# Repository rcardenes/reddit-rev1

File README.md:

Reddit review
=============

Some guy at Reddit asked for some help routing some schematic he came up with. I'm by no
means an expert, but here's my try at it.

It's bit packed (resistors too close to each other, I guess), but I went for compactness
and I don't expect the signals to be high speed by any definition. The point here was
just to show a way to route that big bunch of traces between the 74LS574s.

Top:

Bottom:

Model:

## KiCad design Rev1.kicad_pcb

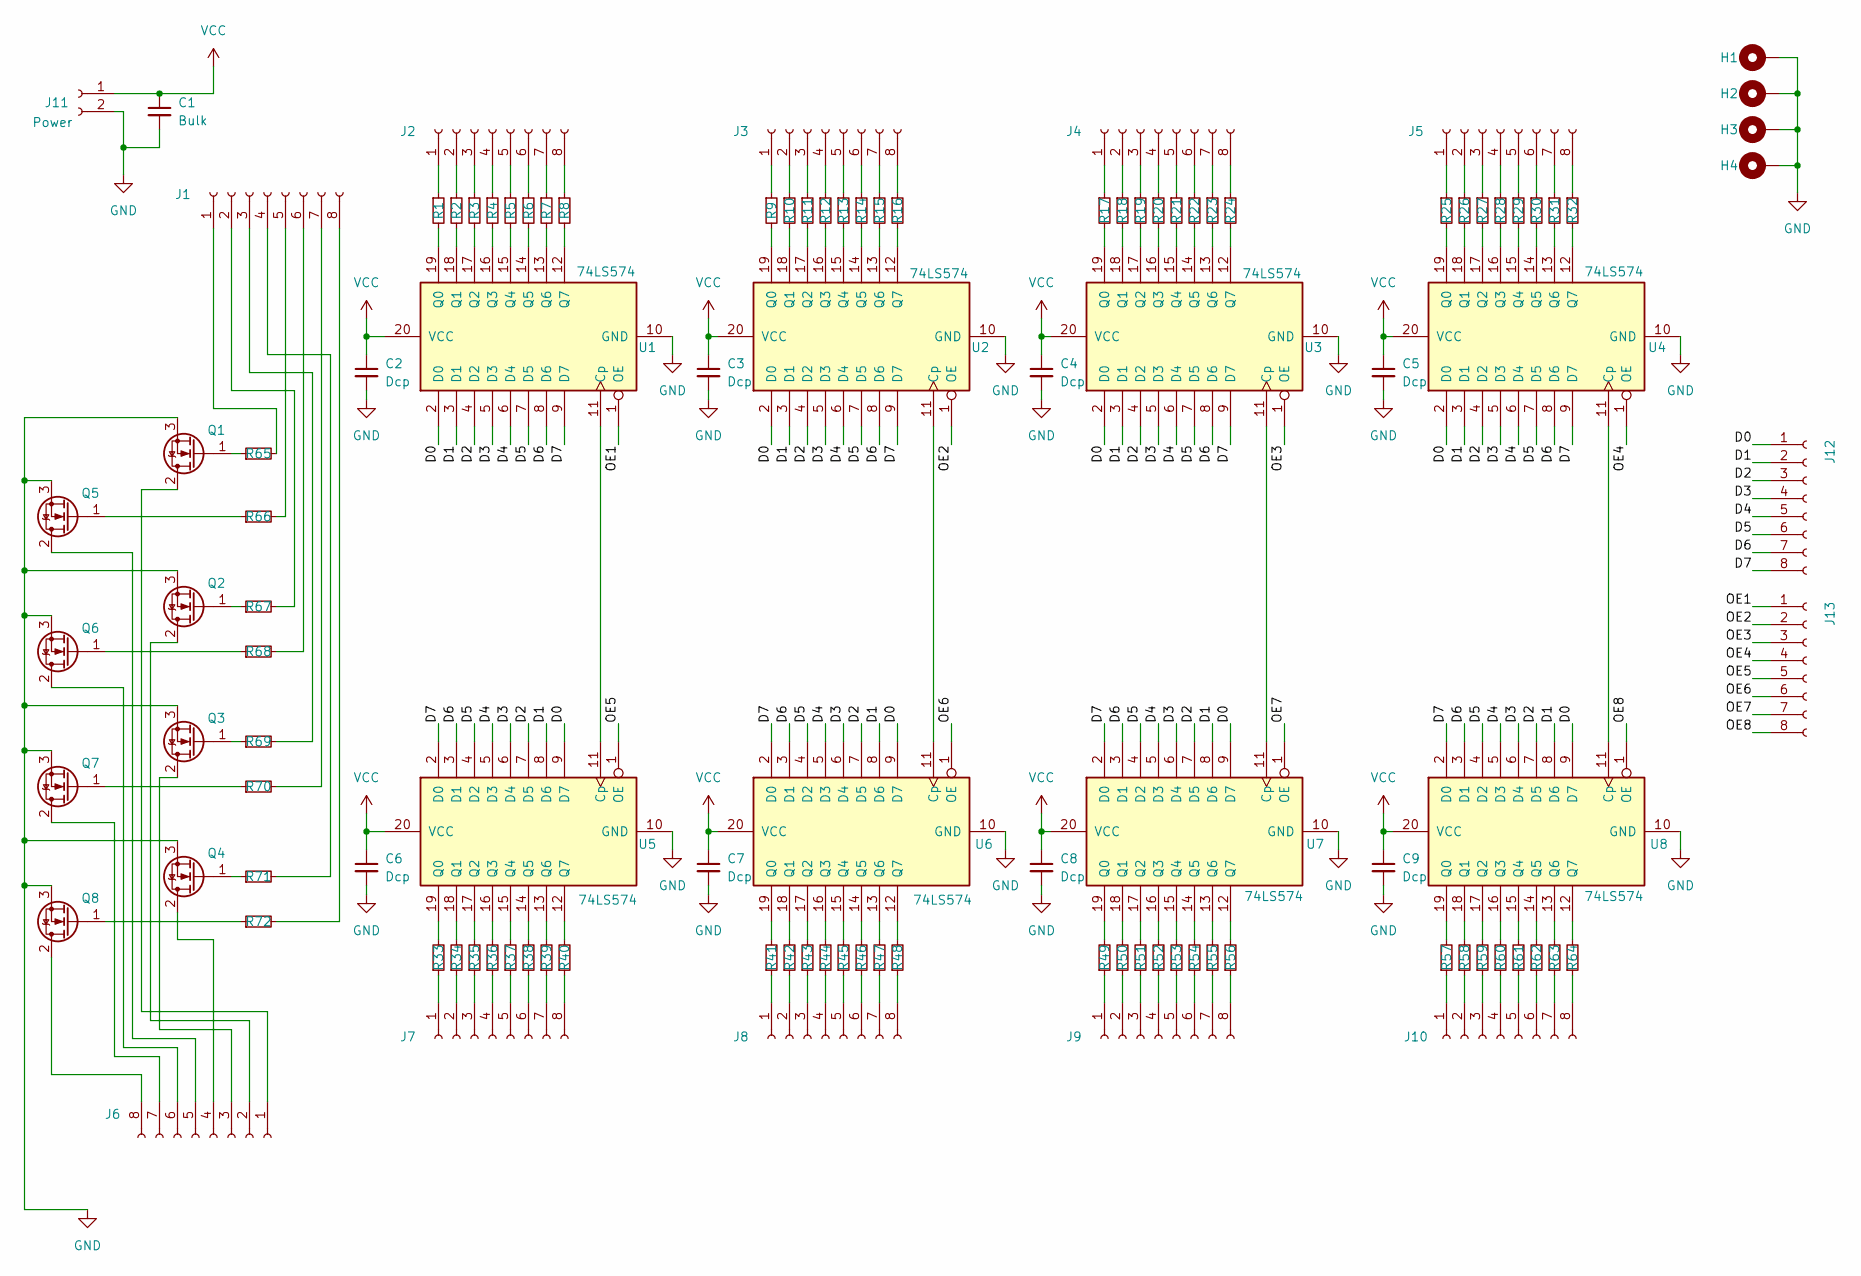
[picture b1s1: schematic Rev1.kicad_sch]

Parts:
C1: Bulk; C_Radial_D6.3mm_H7.0mm_P2.50mm
C2, C3, C4, C5, C6, C7, C8, C9: Dcp; C_Disc_D3.0mm_W2.0mm_P2.50mm
H1, H2, H3, H4: MountingHole_Pad; MountingHole_2.2mm_M2_Pad
J1, J2, J3, J4, J5, J6, J7, J8, J9, J10, J12, J13: Conn_01x08_Socket; PinHeader_1x08_P1.27mm_Vertical
J11: Power; PinHeader_1x02_P1.27mm_Vertical
Q1, Q2, Q3, Q4, Q5, Q6, Q7, Q8: IRF540N; TO-220-3_Vertical
R1, R2, R3, R4, R5, R6, R7, R8, R9, R10, R11, R12, R13, R14, R15, R16, R17, R18, R19, R20, R21, R22, R23, R24, R25, R26, R27, R28, R29, R30, R31, R32, R33, R34, R35, R36, R37, R38, R39, R40, R41, R42, R43, R44, R45, R46, R47, R48, R49, R50, R51, R52, R53, R54, R55, R56, R57, R58, R59, R60, R61, R62, R63, R64, R65, R66, R67, R68, R69, R70, R71, R72: R_Small; R_Axial_DIN0204_L3.6mm_D1.6mm_P5.08mm_Horizontal
U1, U2, U3, U4, U5, U6, U7, U8: 74LS574; DIP-20_W7.62mm

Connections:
/D0: J12.1, U1.2 (D0), U2.2 (D0), U3.2 (D0), U4.2 (D0), U5.9 (D7), U6.9 (D7), U7.9 (D7), U8.9 (D7)
/D1: J12.2, U1.3 (D1), U2.3 (D1), U3.3 (D1), U4.3 (D1), U5.8 (D6), U6.8 (D6), U7.8 (D6), U8.8 (D6)
/D2: J12.3, U1.4 (D2), U2.4 (D2), U3.4 (D2), U4.4 (D2), U5.7 (D5), U6.7 (D5), U7.7 (D5), U8.7 (D5)
/D3: J12.4, U1.5 (D3), U2.5 (D3), U3.5 (D3), U4.5 (D3), U5.6 (D4), U6.6 (D4), U7.6 (D4), U8.6 (D4)
/D4: J12.5, U1.6 (D4), U2.6 (D4), U3.6 (D4), U4.6 (D4), U5.5 (D3), U6.5 (D3), U7.5 (D3), U8.5 (D3)
/D5: J12.6, U1.7 (D5), U2.7 (D5), U3.7 (D5), U4.7 (D5), U5.4 (D2), U6.4 (D2), U7.4 (D2), U8.4 (D2)
/D6: J12.7, U1.8 (D6), U2.8 (D6), U3.8 (D6), U4.8 (D6), U5.3 (D1), U6.3 (D1), U7.3 (D1), U8.3 (D1)
/D7: J12.8, U1.9 (D7), U2.9 (D7), U3.9 (D7), U4.9 (D7), U5.2 (D0), U6.2 (D0), U7.2 (D0), U8.2 (D0)
/OE1: J13.1, U1.1 (OE)
/OE2: J13.2, U2.1 (OE)
/OE3: J13.3, U3.1 (OE)
/OE4: J13.4, U4.1 (OE)
/OE5: J13.5, U5.1 (OE)
/OE6: J13.6, U6.1 (OE)
/OE7: J13.7, U7.1 (OE)
/OE8: J13.8, U8.1 (OE)
GND: C1.2, C2.2, C3.2, C4.2, C5.2, C6.2, C7.2, C8.2, C9.2, H1.1, H2.1, H3.1, H4.1, J11.2, Q1.3 (S), Q2.3 (S), Q3.3 (S), Q4.3 (S), Q5.3 (S), Q6.3 (S), Q7.3 (S), Q8.3 (S), U1.10 (GND), U2.10 (GND), U3.10 (GND), U4.10 (GND), U5.10 (GND), U6.10 (GND), U7.10 (GND), U8.10 (GND)
unnamed: J1.1, R65.2
unnamed: J1.2, R67.2
unnamed: J1.3, R69.2
unnamed: J1.4, R71.2
unnamed: J1.5, R66.2
unnamed: J1.6, R68.2
unnamed: J1.7, R70.2
unnamed: J1.8, R72.2
unnamed: J2.1, R1.1
unnamed: J2.2, R2.1
unnamed: J2.3, R3.1
unnamed: J2.4, R4.1
unnamed: J2.5, R5.1
unnamed: J2.6, R6.1
unnamed: J2.7, R7.1
unnamed: J2.8, R8.1
unnamed: J3.1, R9.1
unnamed: J3.2, R10.1
unnamed: J3.3, R11.1
unnamed: J3.4, R12.1
unnamed: J3.5, R13.1
unnamed: J3.6, R14.1
unnamed: J3.7, R15.1
unnamed: J3.8, R16.1
unnamed: J4.1, R17.1
unnamed: J4.2, R18.1
unnamed: J4.3, R19.1
unnamed: J4.4, R20.1
unnamed: J4.5, R21.1
unnamed: J4.6, R22.1
unnamed: J4.7, R23.1
unnamed: J4.8, R24.1
unnamed: J5.1, R25.1
unnamed: J5.2, R26.1
unnamed: J5.3, R27.1
unnamed: J5.4, R28.1
unnamed: J5.5, R29.1
unnamed: J5.6, R30.1
unnamed: J5.7, R31.1
unnamed: J5.8, R32.1
unnamed: J6.1, Q1.2 (D)
unnamed: J6.2, Q2.2 (D)
unnamed: J6.3, Q3.2 (D)
unnamed: J6.4, Q4.2 (D)
unnamed: J6.5, Q5.2 (D)
unnamed: J6.6, Q6.2 (D)
unnamed: J6.7, Q7.2 (D)
unnamed: J6.8, Q8.2 (D)
unnamed: J7.1, R33.1
unnamed: J7.2, R34.1
unnamed: J7.3, R35.1
unnamed: J7.4, R36.1
unnamed: J7.5, R37.1
unnamed: J7.6, R38.1
unnamed: J7.7, R39.1
unnamed: J7.8, R40.1
unnamed: J8.1, R41.1
unnamed: J8.2, R42.1
unnamed: J8.3, R43.1
unnamed: J8.4, R44.1
unnamed: J8.5, R45.1
unnamed: J8.6, R46.1
unnamed: J8.7, R47.1
unnamed: J8.8, R48.1
unnamed: J9.1, R49.1
unnamed: J9.2, R50.1
unnamed: J9.3, R51.1
unnamed: J9.4, R52.1
unnamed: J9.5, R53.1
unnamed: J9.6, R54.1
unnamed: J9.7, R55.1
unnamed: J9.8, R56.1
unnamed: J10.1, R57.1
unnamed: J10.2, R58.1
unnamed: J10.3, R59.1
unnamed: J10.4, R60.1
unnamed: J10.5, R61.1
unnamed: J10.6, R62.1
unnamed: J10.7, R63.1
unnamed: J10.8, R64.1
unnamed: Q1.1 (G), R65.1
unnamed: Q2.1 (G), R67.1
unnamed: Q3.1 (G), R69.1
unnamed: Q4.1 (G), R71.1
unnamed: Q5.1 (G), R66.1
unnamed: Q6.1 (G), R68.1
unnamed: Q7.1 (G), R70.1
unnamed: Q8.1 (G), R72.1
unnamed: U1.11 (Cp), U5.11 (Cp)
unnamed: R1.2, U1.19 (Q0)
unnamed: R2.2, U1.18 (Q1)
unnamed: R3.2, U1.17 (Q2)
unnamed: R4.2, U1.16 (Q3)
unnamed: R5.2, U1.15 (Q4)
unnamed: R6.2, U1.14 (Q5)
unnamed: R7.2, U1.13 (Q6)
unnamed: R8.2, U1.12 (Q7)
unnamed: U2.11 (Cp), U6.11 (Cp)
unnamed: R9.2, U2.19 (Q0)
unnamed: R10.2, U2.18 (Q1)
unnamed: R11.2, U2.17 (Q2)
unnamed: R12.2, U2.16 (Q3)
unnamed: R13.2, U2.15 (Q4)
unnamed: R14.2, U2.14 (Q5)
unnamed: R15.2, U2.13 (Q6)
unnamed: R16.2, U2.12 (Q7)
unnamed: U3.11 (Cp), U7.11 (Cp)
unnamed: R17.2, U3.19 (Q0)
unnamed: R18.2, U3.18 (Q1)
unnamed: R19.2, U3.17 (Q2)
unnamed: R20.2, U3.16 (Q3)
unnamed: R21.2, U3.15 (Q4)
unnamed: R22.2, U3.14 (Q5)
unnamed: R23.2, U3.13 (Q6)
unnamed: R24.2, U3.12 (Q7)
unnamed: U4.11 (Cp), U8.11 (Cp)
unnamed: R25.2, U4.19 (Q0)
unnamed: R26.2, U4.18 (Q1)
unnamed: R27.2, U4.17 (Q2)
unnamed: R28.2, U4.16 (Q3)
unnamed: R29.2, U4.15 (Q4)
unnamed: R30.2, U4.14 (Q5)
unnamed: R31.2, U4.13 (Q6)
unnamed: R32.2, U4.12 (Q7)
unnamed: R33.2, U5.19 (Q0)
unnamed: R34.2, U5.18 (Q1)
unnamed: R35.2, U5.17 (Q2)
unnamed: R36.2, U5.16 (Q3)
unnamed: R37.2, U5.15 (Q4)
unnamed: R38.2, U5.14 (Q5)
unnamed: R39.2, U5.13 (Q6)
unnamed: R40.2, U5.12 (Q7)
unnamed: R41.2, U6.19 (Q0)
unnamed: R42.2, U6.18 (Q1)
unnamed: R43.2, U6.17 (Q2)
unnamed: R44.2, U6.16 (Q3)
unnamed: R45.2, U6.15 (Q4)
unnamed: R46.2, U6.14 (Q5)
unnamed: R47.2, U6.13 (Q6)
unnamed: R48.2, U6.12 (Q7)
unnamed: R49.2, U7.19 (Q0)
unnamed: R50.2, U7.18 (Q1)
unnamed: R51.2, U7.17 (Q2)
unnamed: R52.2, U7.16 (Q3)
unnamed: R53.2, U7.15 (Q4)
unnamed: R54.2, U7.14 (Q5)
unnamed: R55.2, U7.13 (Q6)
unnamed: R56.2, U7.12 (Q7)
unnamed: R57.2, U8.19 (Q0)
unnamed: R58.2, U8.18 (Q1)
unnamed: R59.2, U8.17 (Q2)
unnamed: R60.2, U8.16 (Q3)
unnamed: R61.2, U8.15 (Q4)
unnamed: R62.2, U8.14 (Q5)
unnamed: R63.2, U8.13 (Q6)
unnamed: R64.2, U8.12 (Q7)
VCC: C1.1, C2.1, C3.1, C4.1, C5.1, C6.1, C7.1, C8.1, C9.1, J11.1, U1.20 (VCC), U2.20 (VCC), U3.20 (VCC), U4.20 (VCC), U5.20 (VCC), U6.20 (VCC), U7.20 (VCC), U8.20 (VCC)

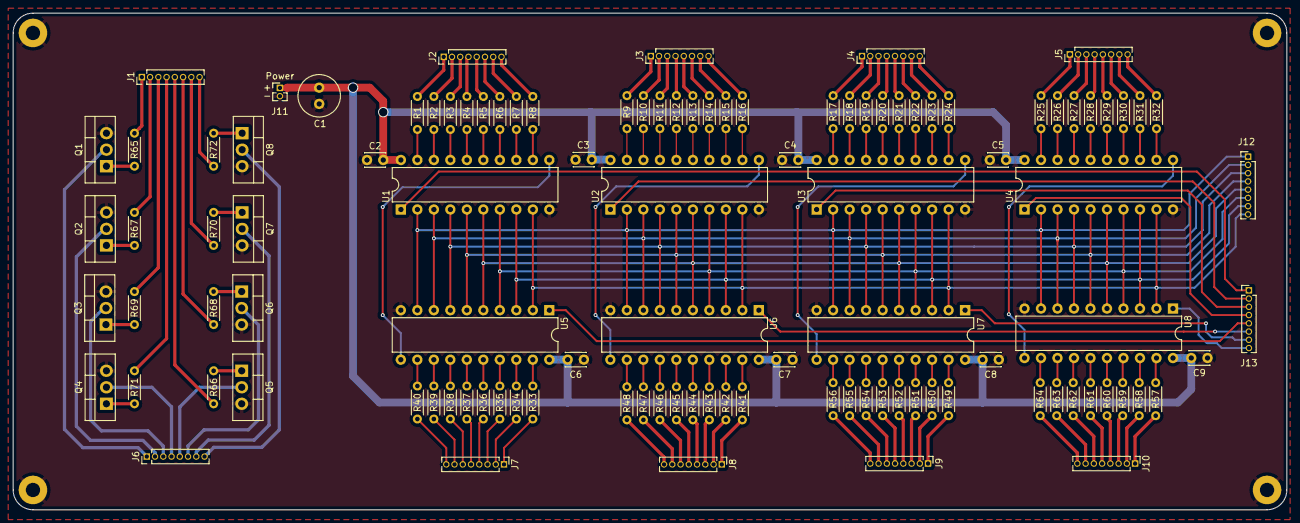
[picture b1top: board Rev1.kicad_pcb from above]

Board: 2 copper layers, 196.1 x 76.5 mm, 114 parts (0 on the bottom side), 174 nets.

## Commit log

2024-09-24 Update, pics
2024-09-24 Update README.md with captures
2024-09-25 Thinner data traces, to increase the distance to the IC pins
2024-09-26 Added decoupling caps. Rerouted
2024-09-26 Regenerated the pics
